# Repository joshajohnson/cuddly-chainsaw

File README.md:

# Cuddly Chainsaw

A split 65% keyboard with macro column, per key RGB, and rotary encoders. Running on QMK.

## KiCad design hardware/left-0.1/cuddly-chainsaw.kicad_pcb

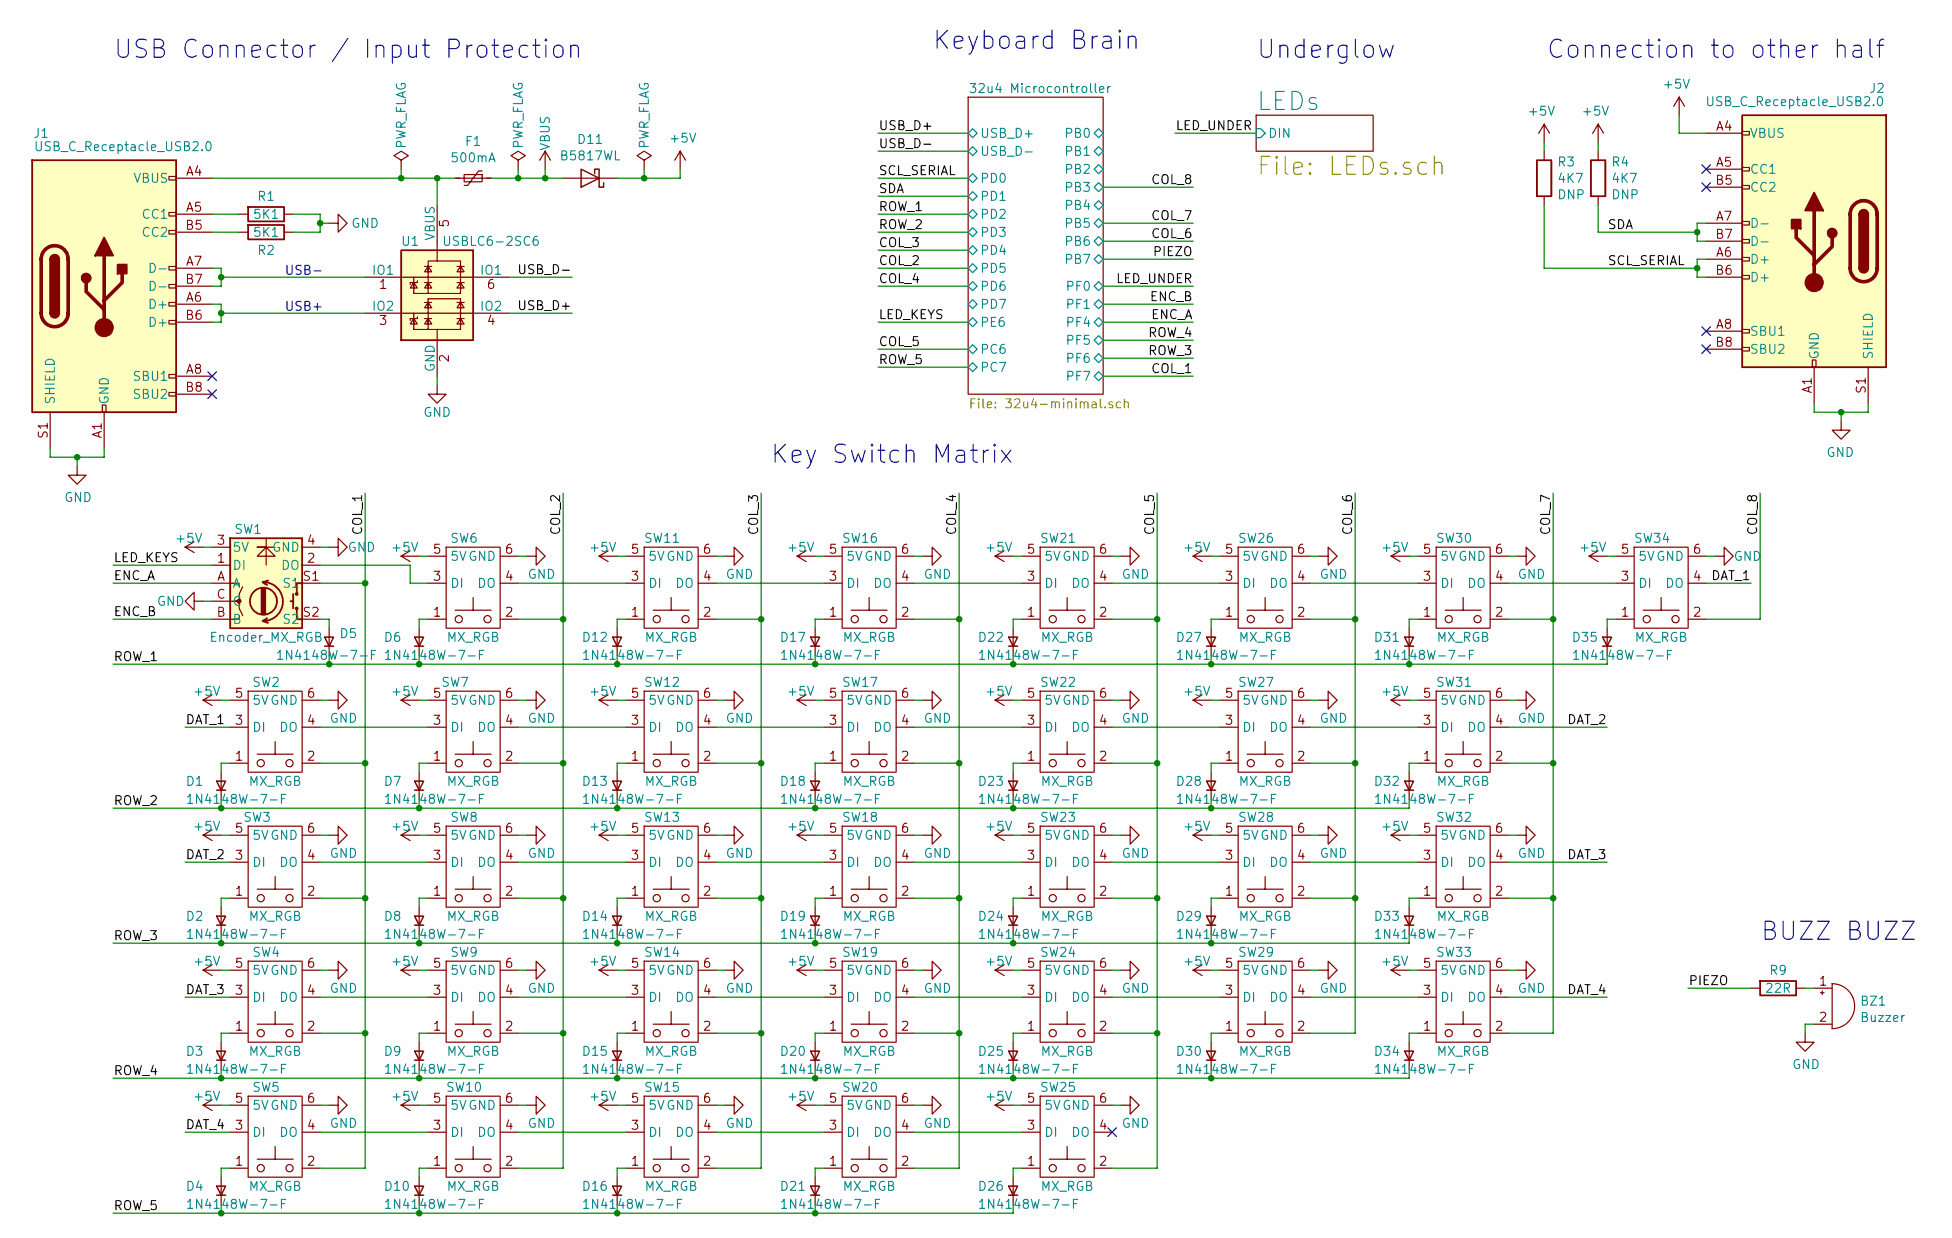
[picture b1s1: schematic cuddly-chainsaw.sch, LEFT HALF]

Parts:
BZ1: Buzzer; Buzzer_Murata_PKMCS0909E4000-R1; MPN PKMCS0909E4000; Digikey 490-9647-1-ND
D1, D2, D3, D4, D5, D6, D7, D8, D9, D10, D12, D13, D14, D15, D16, D17, D18, D19, D20, D21, D22, D23, D24, D25, D26, D27, D28, D29, D30, D31, D32, D33, D34, D35: 1N4148W-7-F; D_SOD-123; MPN 1N4148W-7-F; Digikey 1N4148W-FDICT-ND
D11: B5817WL; D_SOD-123F; MPN B5817WL; Digikey SDM1100S1F-7DICT-ND
F1: 500mA; Fuse_0805_2012Metric; MPN 0ZCK0050FF2E; Digikey 507-1813-1-ND
J1, J2: USB_C_Receptacle_USB2.0; USB_C_U262-161N-4BVC11; MPN U262-161N-4BVC11; Digikey NA
R1, R2: 5K1; R_0603_1608Metric; MPN CR0603-JW-512ELF; Digikey 118-CR0603-JW-512ELFCT-ND
R3, R4: 4K7; R_0603_1608Metric
R9: 22R; R_0603_1608Metric
SW1: Encoder_MX_RGB; MX_KEYSWITCH_ENCODER_RGB; MPN EC11E1834403; Digikey 987-1398-ND
SW2, SW3, SW4, SW5, SW6, SW11, SW12, SW13, SW14, SW16, SW17, SW18, SW19, SW21, SW22, SW23, SW24, SW26, SW27, SW28, SW29, SW30, SW31, SW32, SW33, SW34: MX_RGB; MX_KEYSWITCH_RGB
SW7: MX_RGB; MX_KEYSWITCH_RGB_1.5U
SW8: MX_RGB; MX_KEYSWITCH_RGB_1.75U
SW9: MX_RGB; MX_KEYSWITCH_RGB_2.25U
SW10, SW15, SW20: MX_RGB; MX_KEYSWITCH_RGB_1.25U
SW25: MX_RGB; MX_KEYSWITCH_RGB_2.75U_REV_STABS
U1: USBLC6-2SC6; SOT-23-6; MPN USBLC6-2SC6; Digikey 497-5235-1-ND

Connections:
+5V: D11.1 (K), J2.A4 (VBUS), J2.A9 (VBUS), J2.B4 (VBUS), J2.B9 (VBUS), R3.1, R4.1, SW1.3 (5V), SW2.5 (5V), SW3.5 (5V), SW4.5 (5V), SW5.5 (5V), SW6.5 (5V), SW7.5 (5V), SW8.5 (5V), SW9.5 (5V), SW10.5 (5V), SW11.5 (5V), SW12.5 (5V), SW13.5 (5V), SW14.5 (5V), SW15.5 (5V), SW16.5 (5V), SW17.5 (5V), SW18.5 (5V), SW19.5 (5V), SW20.5 (5V), SW21.5 (5V), SW22.5 (5V), SW23.5 (5V), SW24.5 (5V), SW25.5 (5V), SW26.5 (5V), SW27.5 (5V), SW28.5 (5V), SW29.5 (5V), SW30.5 (5V), SW31.5 (5V), SW32.5 (5V), SW33.5 (5V), SW34.5 (5V); also elsewhere on the board
/COL_1: SW1.S1, SW2.2, SW3.2, SW4.2, SW5.2; also elsewhere on the board
/COL_2: SW6.2, SW7.2, SW8.2, SW9.2, SW10.2; also elsewhere on the board
/COL_3: SW11.2, SW12.2, SW13.2, SW14.2, SW15.2; also elsewhere on the board
/COL_4: SW16.2, SW17.2, SW18.2, SW19.2, SW20.2; also elsewhere on the board
/COL_5: SW21.2, SW22.2, SW23.2, SW24.2, SW25.2; also elsewhere on the board
/COL_6: SW26.2, SW27.2, SW28.2, SW29.2; also elsewhere on the board
/COL_7: SW30.2, SW31.2, SW32.2, SW33.2; also elsewhere on the board
/COL_8: SW34.2; also elsewhere on the board
/DAT_1: SW2.3 (DI), SW34.4 (DO)
/DAT_2: SW3.3 (DI), SW31.4 (DO)
/DAT_3: SW4.3 (DI), SW32.4 (DO)
/DAT_4: SW5.3 (DI), SW33.4 (DO)
/ENC_A: SW1.A; also elsewhere on the board
/ENC_B: SW1.B; also elsewhere on the board
/LED_KEYS: SW1.1 (DI); also elsewhere on the board
/PIEZO: R9.2; also elsewhere on the board
/ROW_1: D5.1 (K), D6.1 (K), D12.1 (K), D17.1 (K), D22.1 (K), D27.1 (K), D31.1 (K), D35.1 (K); also elsewhere on the board
/ROW_2: D1.1 (K), D7.1 (K), D13.1 (K), D18.1 (K), D23.1 (K), D28.1 (K), D32.1 (K); also elsewhere on the board
/ROW_3: D2.1 (K), D8.1 (K), D14.1 (K), D19.1 (K), D24.1 (K), D29.1 (K), D33.1 (K); also elsewhere on the board
/ROW_4: D3.1 (K), D9.1 (K), D15.1 (K), D20.1 (K), D25.1 (K), D30.1 (K), D34.1 (K); also elsewhere on the board
/ROW_5: D4.1 (K), D10.1 (K), D16.1 (K), D21.1 (K), D26.1 (K); also elsewhere on the board
/SCL_SERIAL: J2.A6 (D+), J2.B6 (D+), R3.2; also elsewhere on the board
/SDA: J2.A7 (D-), J2.B7 (D-), R4.2; also elsewhere on the board
/USB_D+: U1.4 (IO2); also elsewhere on the board
/USB_D-: U1.6 (IO1); also elsewhere on the board
GND: BZ1.2 (+), J1.A1 (GND), J1.A12 (GND), J1.B1 (GND), J1.B12 (GND), J1.S1 (SHIELD), J2.A1 (GND), J2.A12 (GND), J2.B1 (GND), J2.B12 (GND), J2.S1 (SHIELD), R1.1, R2.1, SW1.4 (GND), SW1.C, SW2.6 (GND), SW3.6 (GND), SW4.6 (GND), SW5.6 (GND), SW6.6 (GND), SW7.6 (GND), SW8.6 (GND), SW9.6 (GND), SW10.6 (GND), SW11.6 (GND), SW12.6 (GND), SW13.6 (GND), SW14.6 (GND), SW15.6 (GND), SW16.6 (GND), SW17.6 (GND), SW18.6 (GND), SW19.6 (GND), SW20.6 (GND), SW21.6 (GND), SW22.6 (GND), SW23.6 (GND), SW24.6 (GND), SW25.6 (GND), SW26.6 (GND), SW27.6 (GND), SW28.6 (GND), SW29.6 (GND), SW30.6 (GND), SW31.6 (GND), SW32.6 (GND), SW33.6 (GND), SW34.6 (GND), U1.2 (GND); also elsewhere on the board
unnamed: BZ1.1 (-), R9.1
unnamed: D1.2 (A), SW2.1
unnamed: D2.2 (A), SW3.1
unnamed: D3.2 (A), SW4.1
unnamed: D4.2 (A), SW5.1
unnamed: D5.2 (A), SW1.S2
unnamed: D6.2 (A), SW6.1
unnamed: D7.2 (A), SW7.1
unnamed: D8.2 (A), SW8.1
unnamed: D9.2 (A), SW9.1
unnamed: D10.2 (A), SW10.1
unnamed: D12.2 (A), SW11.1
unnamed: D13.2 (A), SW12.1
unnamed: D14.2 (A), SW13.1
unnamed: D15.2 (A), SW14.1
unnamed: D16.2 (A), SW15.1
unnamed: D17.2 (A), SW16.1
unnamed: D18.2 (A), SW17.1
unnamed: D19.2 (A), SW18.1
unnamed: D20.2 (A), SW19.1
unnamed: D21.2 (A), SW20.1
unnamed: D22.2 (A), SW21.1
unnamed: D23.2 (A), SW22.1
unnamed: D24.2 (A), SW23.1
unnamed: D25.2 (A), SW24.1
unnamed: D26.2 (A), SW25.1
unnamed: D27.2 (A), SW26.1
unnamed: D28.2 (A), SW27.1
unnamed: D29.2 (A), SW28.1
unnamed: D30.2 (A), SW29.1
unnamed: D31.2 (A), SW30.1
unnamed: D32.2 (A), SW31.1
unnamed: D33.2 (A), SW32.1
unnamed: D34.2 (A), SW33.1
unnamed: D35.2 (A), SW34.1
unnamed: F1.2, J1.A4 (VBUS), J1.A9 (VBUS), J1.B4 (VBUS), J1.B9 (VBUS), U1.5 (VBUS)
unnamed: J1.A5 (CC1), R1.2
unnamed: J1.A6 (D+), J1.B6 (D+), U1.3 (IO2)
unnamed: J1.A7 (D-), J1.B7 (D-), U1.1 (IO1)
unnamed: J1.B5 (CC2), R2.2
unnamed: SW1.2 (DO), SW6.3 (DI)
unnamed: SW2.4 (DO), SW7.3 (DI)
unnamed: SW3.4 (DO), SW8.3 (DI)
unnamed: SW4.4 (DO), SW9.3 (DI)
unnamed: SW5.4 (DO), SW10.3 (DI)
unnamed: SW10.4 (DO), SW15.3 (DI)
unnamed: SW6.4 (DO), SW11.3 (DI)
unnamed: SW11.4 (DO), SW16.3 (DI)
unnamed: SW7.4 (DO), SW12.3 (DI)
unnamed: SW12.4 (DO), SW17.3 (DI)
unnamed: SW8.4 (DO), SW13.3 (DI)
unnamed: SW13.4 (DO), SW18.3 (DI)
unnamed: SW9.4 (DO), SW14.3 (DI)
unnamed: SW14.4 (DO), SW19.3 (DI)
unnamed: SW15.4 (DO), SW20.3 (DI)
unnamed: SW16.4 (DO), SW21.3 (DI)
unnamed: SW17.4 (DO), SW22.3 (DI)
unnamed: SW18.4 (DO), SW23.3 (DI)
unnamed: SW19.4 (DO), SW24.3 (DI)
unnamed: SW20.4 (DO), SW25.3 (DI)
unnamed: SW21.4 (DO), SW26.3 (DI)
unnamed: SW22.4 (DO), SW27.3 (DI)
unnamed: SW23.4 (DO), SW28.3 (DI)
unnamed: SW24.4 (DO), SW29.3 (DI)
unnamed: SW26.4 (DO), SW30.3 (DI)
unnamed: SW27.4 (DO), SW31.3 (DI)
unnamed: SW28.4 (DO), SW32.3 (DI)
unnamed: SW29.4 (DO), SW33.3 (DI)
unnamed: SW30.4 (DO), SW34.3 (DI)
VBUS: D11.2 (A), F1.1; also elsewhere on the board

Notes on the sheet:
USB Connector / Input Protection
USB+
USB-
Connection to other half
Keyboard Brain
Key Switch Matrix
BUZZ BUZZ
Underglow

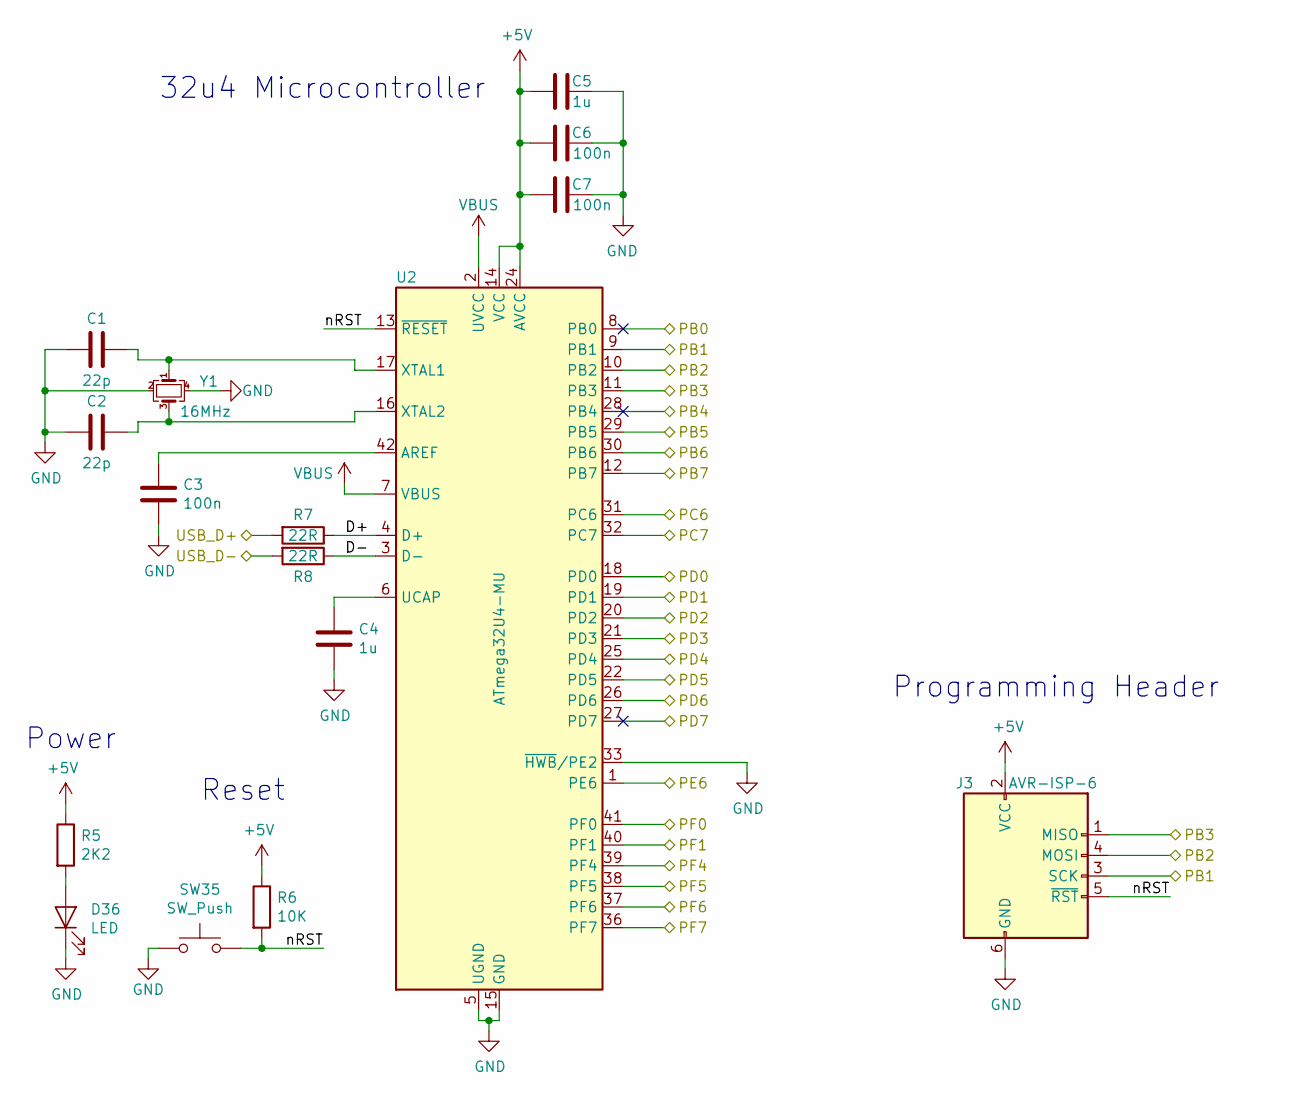
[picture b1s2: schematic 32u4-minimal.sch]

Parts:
C1, C2: 22p; C_0603_1608Metric; MPN CL10C220JB8NFNC; Digikey 1276-2228-1-ND
C3, C6, C7: 100n; C_0603_1608Metric; MPN CL10B104KB8NNNC; Digikey 1276-1000-1-ND
C4, C5: 1u; C_0603_1608Metric; MPN CL10A105MP8NNNC; Digikey 1276-1866-1-ND
D36: LED; LED_0603_1608Metric_Castellated; MPN 150060VS75000; Digikey 732-4980-1-ND
J3: AVR-ISP-6; AVR_PROG_2.54_SMT
R5: 2K2; R_0603_1608Metric; MPN CR0603-JW-222ELF; Digikey CR0603-JW-222ELFCT-ND
R6: 10K; R_0603_1608Metric; MPN CR0603-JW-103ELF; Digikey CR0603-JW-103ELFCT-ND
R7, R8: 22R; R_0603_1608Metric; MPN CR0603-JW-220ELF; Digikey CR0603-JW-220ELFCT-ND
SW35: SW_Push; SW_Push_PTS820; MPN KSR223GLFG; Digikey 401-1704-1-ND
U2: ATmega32U4-MU; QFN-44-1EP_7x7mm_P0.5mm_EP5.2x5.2mm
Y1: 16MHz; Crystal_SMD_3225-4Pin_3.2x2.5mm; MPN ABM8-16.000MHZ-B2-T; Digikey 535-9134-1-ND

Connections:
+5V: C5.1, C6.1, C7.1, J3.2 (VCC), R5.1, R6.1, U2.14 (VCC), U2.24 (AVCC), U2.34 (VCC), U2.44 (AVCC); also elsewhere on the board
/32u4 Microcontroller/D+: R7.1, U2.4 (D+)
/32u4 Microcontroller/D-: R8.1, U2.3 (D-)
/32u4 Microcontroller/PB1: J3.3 (SCK), U2.9 (PB1)
/32u4 Microcontroller/PB2: J3.4 (MOSI), U2.10 (PB2)
/32u4 Microcontroller/nRST: J3.5 (~RST), R6.2, SW35.2, U2.13 (~RESET)
/COL_1: U2.36 (PF7); also elsewhere on the board
/COL_2: U2.22 (PD5); also elsewhere on the board
/COL_3: U2.25 (PD4); also elsewhere on the board
/COL_4: U2.26 (PD6); also elsewhere on the board
/COL_5: U2.31 (PC6); also elsewhere on the board
/COL_6: U2.30 (PB6); also elsewhere on the board
/COL_7: U2.29 (PB5); also elsewhere on the board
/COL_8: J3.1 (MISO), U2.11 (PB3); also elsewhere on the board
/ENC_A: U2.39 (PF4); also elsewhere on the board
/ENC_B: U2.40 (PF1); also elsewhere on the board
/LED_KEYS: U2.1 (PE6); also elsewhere on the board
/LED_UNDER: U2.41 (PF0); also elsewhere on the board
/PIEZO: U2.12 (PB7); also elsewhere on the board
/ROW_1: U2.20 (PD2); also elsewhere on the board
/ROW_2: U2.21 (PD3); also elsewhere on the board
/ROW_3: U2.37 (PF6); also elsewhere on the board
/ROW_4: U2.38 (PF5); also elsewhere on the board
/ROW_5: U2.32 (PC7); also elsewhere on the board
/SCL_SERIAL: U2.18 (PD0); also elsewhere on the board
/SDA: U2.19 (PD1); also elsewhere on the board
/USB_D+: R7.2; also elsewhere on the board
/USB_D-: R8.2; also elsewhere on the board
GND: C1.2, C2.2, C3.2, C4.2, C5.2, C6.2, C7.2, D36.1 (K), J3.6 (GND), SW35.1, U2.5 (UGND), U2.15 (GND), U2.23 (GND), U2.33 (~HWB~/PE2), U2.35 (GND), U2.43 (GND), U2.45 (GND), Y1.2, Y1.4; also elsewhere on the board
unnamed: C1.1, U2.17 (XTAL1), Y1.1
unnamed: C2.1, U2.16 (XTAL2), Y1.3
unnamed: C3.1, U2.42 (AREF)
unnamed: C4.1, U2.6 (UCAP)
unnamed: D36.2 (A), R5.2
VBUS: U2.2 (UVCC), U2.7 (VBUS); also elsewhere on the board

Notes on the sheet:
Reset
32u4 Microcontroller
Power
Programming Header

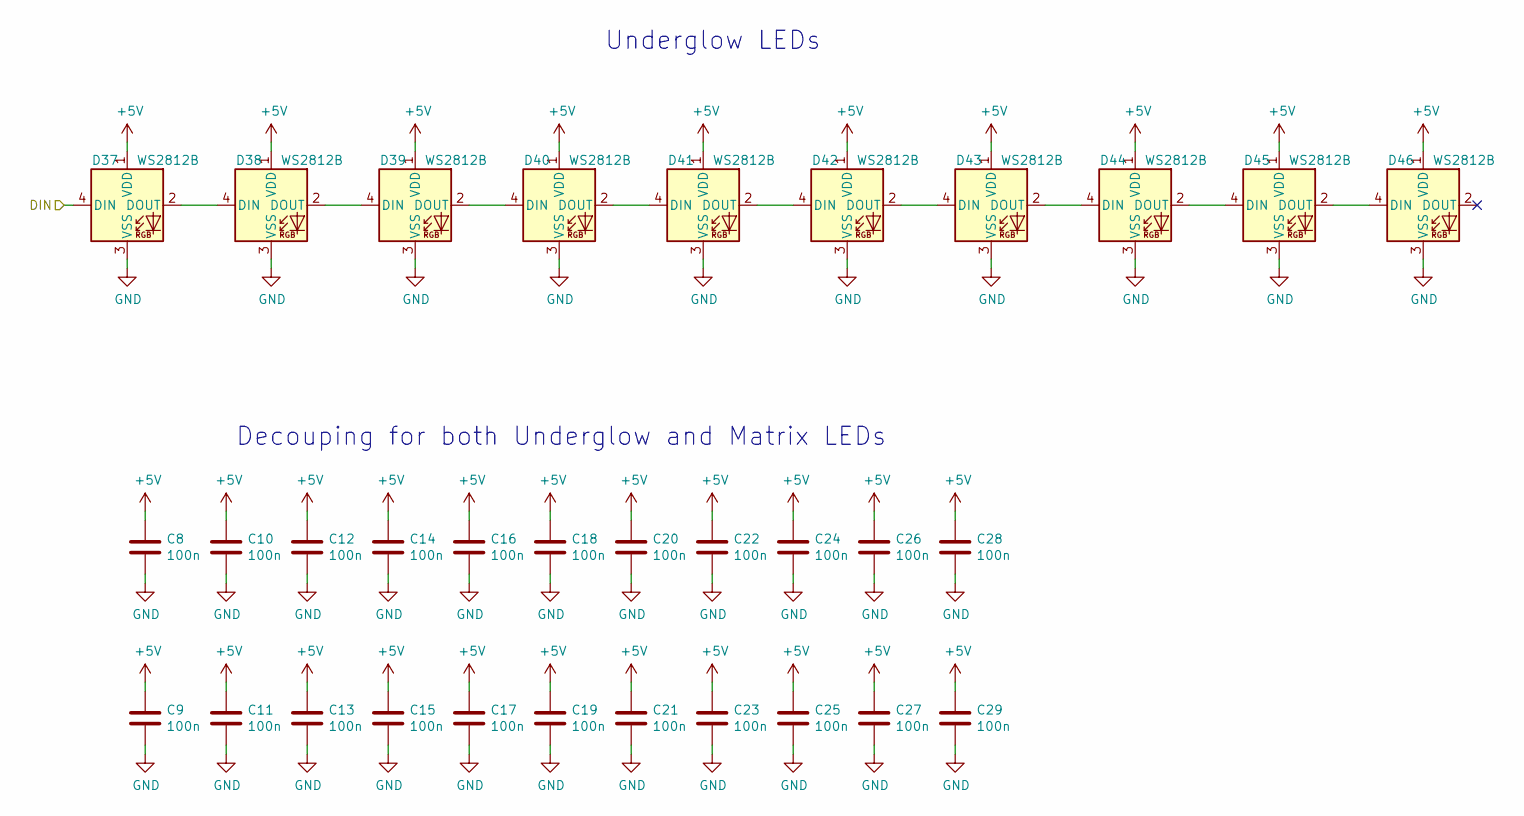
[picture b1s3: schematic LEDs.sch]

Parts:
C8, C9, C10, C11, C12, C13, C14, C15, C16, C17, C18, C19, C20, C21, C22, C23, C24, C25, C26, C27, C28, C29: 100n; C_0603_1608Metric
D37, D38, D39, D40, D41, D42, D43, D44, D45, D46: WS2812B; LED_WS2812B_PLCC4_5.0x5.0mm_P3.2mm

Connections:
+5V: C8.1, C9.1, C10.1, C11.1, C12.1, C13.1, C14.1, C15.1, C16.1, C17.1, C18.1, C19.1, C20.1, C21.1, C22.1, C23.1, C24.1, C25.1, C26.1, C27.1, C28.1, C29.1, D37.1 (VDD), D38.1 (VDD), D39.1 (VDD), D40.1 (VDD), D41.1 (VDD), D42.1 (VDD), D43.1 (VDD), D44.1 (VDD), D45.1 (VDD), D46.1 (VDD); also elsewhere on the board
/LED_UNDER: D37.4 (DIN); also elsewhere on the board
GND: C8.2, C9.2, C10.2, C11.2, C12.2, C13.2, C14.2, C15.2, C16.2, C17.2, C18.2, C19.2, C20.2, C21.2, C22.2, C23.2, C24.2, C25.2, C26.2, C27.2, C28.2, C29.2, D37.3 (VSS), D38.3 (VSS), D39.3 (VSS), D40.3 (VSS), D41.3 (VSS), D42.3 (VSS), D43.3 (VSS), D44.3 (VSS), D45.3 (VSS), D46.3 (VSS); also elsewhere on the board
unnamed: D37.2 (DOUT), D38.4 (DIN)
unnamed: D38.2 (DOUT), D39.4 (DIN)
unnamed: D39.2 (DOUT), D40.4 (DIN)
unnamed: D40.2 (DOUT), D41.4 (DIN)
unnamed: D41.2 (DOUT), D42.4 (DIN)
unnamed: D42.2 (DOUT), D43.4 (DIN)
unnamed: D43.2 (DOUT), D44.4 (DIN)
unnamed: D44.2 (DOUT), D45.4 (DIN)
unnamed: D45.2 (DOUT), D46.4 (DIN)

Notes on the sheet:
Underglow LEDs
Decouping for both Underglow and Matrix LEDs

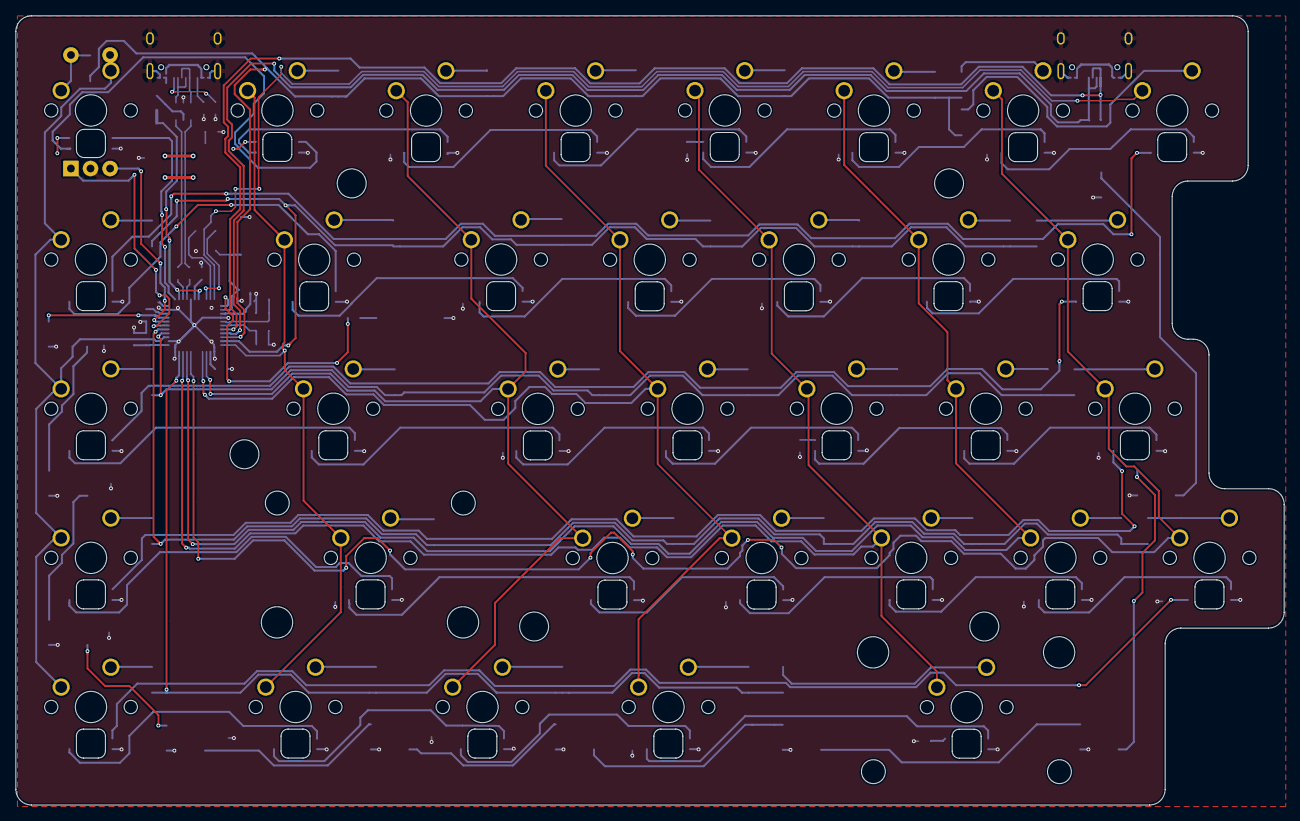
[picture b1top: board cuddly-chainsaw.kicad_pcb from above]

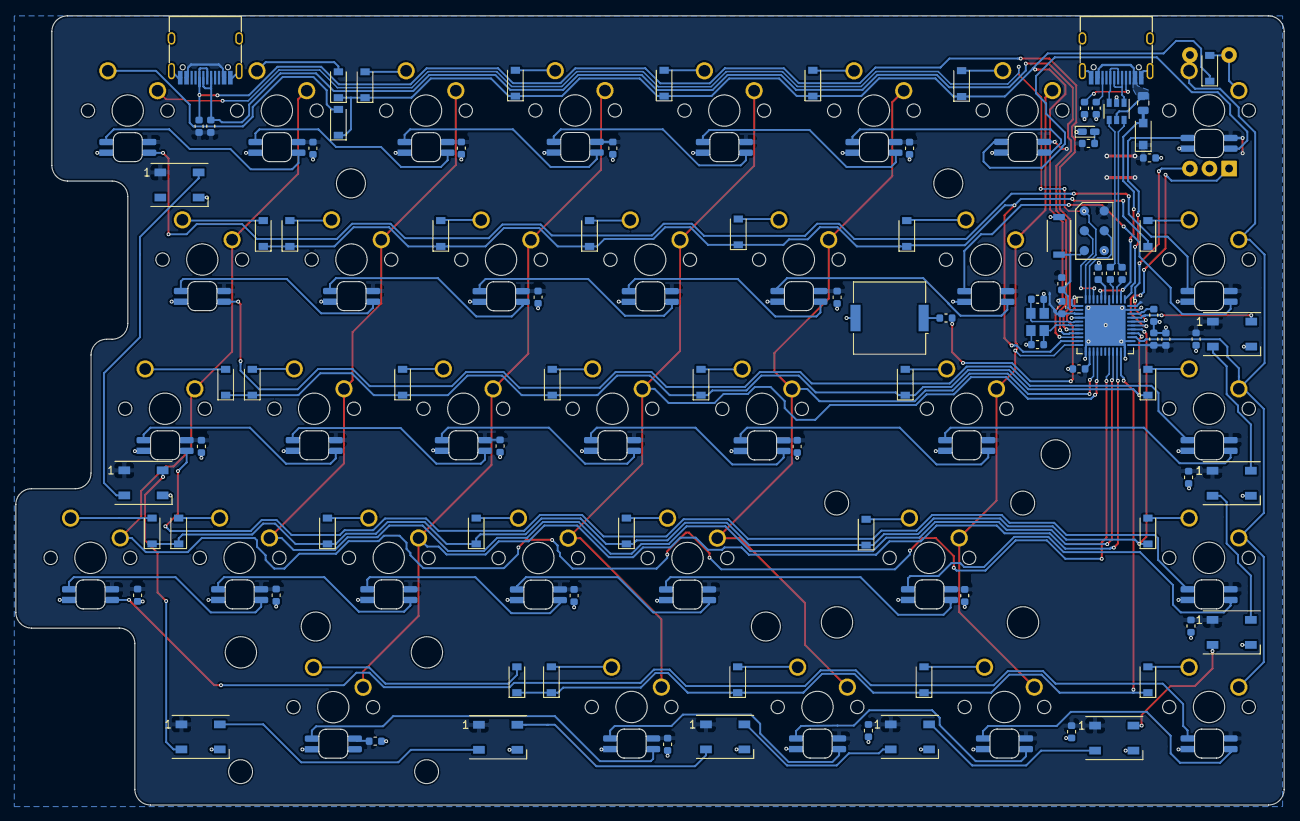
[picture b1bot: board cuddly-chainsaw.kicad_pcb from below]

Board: 2 copper layers, 162.0 x 100.8 mm, 127 parts (93 on the bottom side), 117 nets.

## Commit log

2020-01-09 first pass at schematic
2020-01-09 both halves in pcbnew
2020-01-10 first go at board outline done
2020-01-12 left all connected
2020-01-13 layout looking nice, just graphics to go
2020-01-14 layout ++
2020-01-15 right half passes drc
2020-01-16 moved mounting oles
2020-01-17 updated components due to jlk change
2020-01-17 update board with new footprints
2020-01-17 abs to rel path
2020-05-24 more layout
